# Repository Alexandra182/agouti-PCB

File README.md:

# Agouti (ñeque) PCB 

## BOM
- [Heart ears LED (reverse mounted)](https://www.tme.eu/ro/details/ost10807c1c-c/diode-led-speciale-cu-efect/optosupply/)
- [Hands LED (reverse mounted)](https://ro.mouser.com/ProductDetail/ams-OSRAM/LO-P47K-K2M1-24-0-R18-Z?qs=w%2Fv1CP2dgqrUwoZD9cFykg%3D%3D)
- [555 timer](https://ro.mouser.com/ProductDetail/Microchip-Technology-Atmel/MIC1555YM5-TR?qs=Y3Q3JoKAO1QTQn1YTyJaSg%3D%3D)
- [Battery holder](https://ro.mouser.com/ProductDetail/712-BAT-HLD-001)
- [Switch](https://ro.mouser.com/ProductDetail/CUI-Devices/DS04-254-2-01BK-SMT?qs=wnTfsH77Xs7VDGZ8jaePmA%3D%3D)

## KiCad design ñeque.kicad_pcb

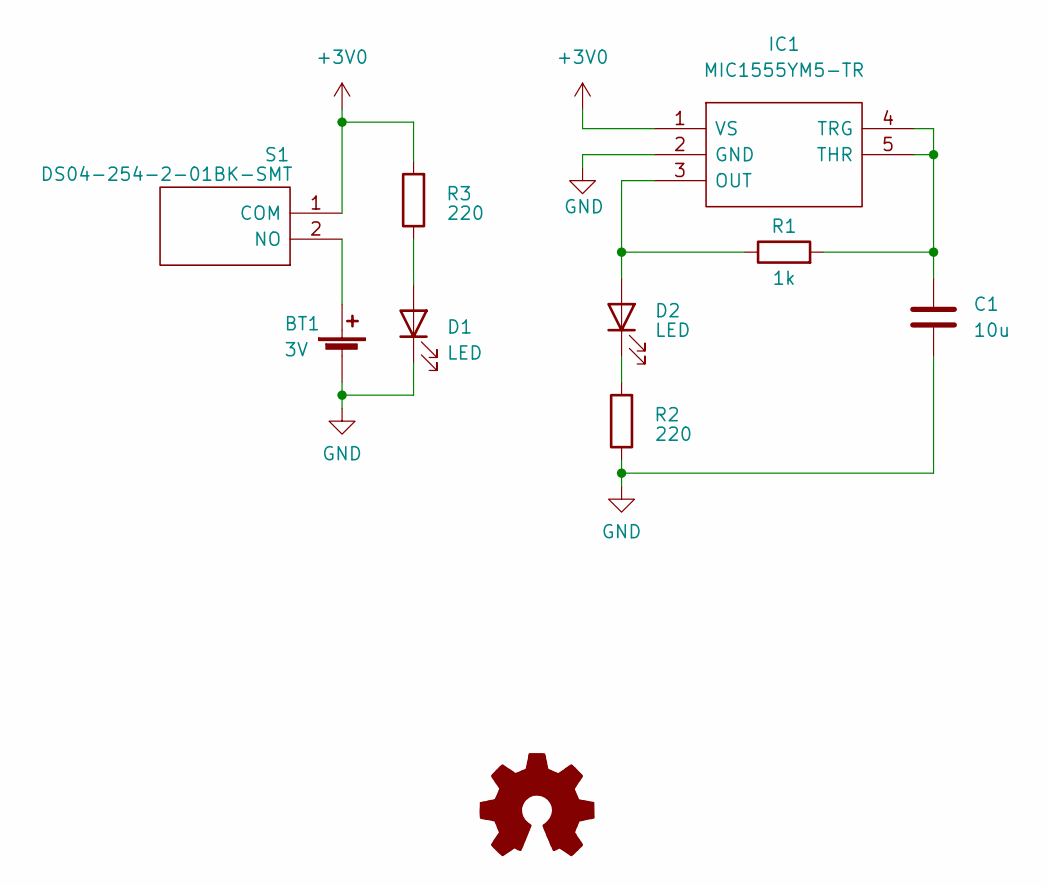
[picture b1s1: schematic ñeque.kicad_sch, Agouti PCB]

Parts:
BT1: 3V; BatteryHolder_Keystone_3034_1x20mm
C1: 10u; C_0603_1608Metric
D1: LED; LED_1206_3216Metric
D2: LED; LOP47KK2M1240R18Z
IC1: MIC1555YM5-TR; SOT95P280X145-5N; Mouser Part Number 998-MIC1555YM5TR
R1: 1k; R_0603_1608Metric
R2, R3: 220; R_0603_1608Metric
S1: DS04-254-2-01BK-SMT; DS04254201BKSMT; Mouser Part Number 490-DS04254201BK-SMT

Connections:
+3V0: IC1.1 (VS), R3.2, S1.1 (COM)
GND: BT1.2 (-), C1.2, D1.1 (K), IC1.2 (GND), R2.1
unnamed: BT1.1 (+), S1.2 (NO)
unnamed: C1.1, IC1.4 (TRG), IC1.5 (THR), R1.2
unnamed: D1.2 (A), R3.1
unnamed: D2.1 (K), R2.2
unnamed: D2.2 (A), IC1.3 (OUT), R1.1

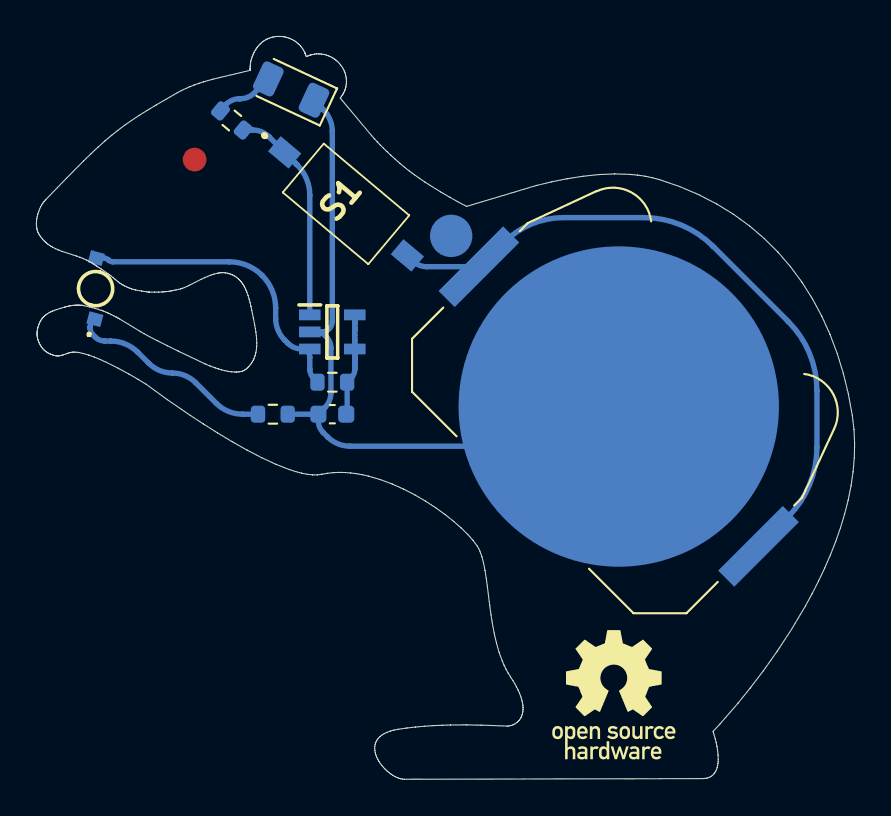
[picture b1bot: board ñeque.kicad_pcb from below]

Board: 2 copper layers, 45.5 x 41.3 mm, 9 parts (9 on the bottom side), 7 nets.

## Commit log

2022-12-09 KiCAD files
2022-12-09 images
2023-01-04 fixed resistor + LED
2023-01-04 Update README.md
    BOM
2023-01-05 updated RC values
